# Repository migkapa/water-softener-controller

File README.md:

# Water Softener Controller (rev A)

> [!WARNING]
> **Design only: not built, not tested, not reviewed by an engineer.**
> Low voltage (12 V DC) only. The relay and the field wiring are not isolated or
> rated for mains. If you build it, check everything yourself first; start with
> [Open items](#open-items).

Full film: [`output/product/water_softener_controller.mp4`](output/product/water_softener_controller.mp4)
(21 s, 1280 x 720, no sound).

| Closed | Wiring bay open | See-through | Exploded |
|---|---|---|---|
|  |  |  |  |

Control board for a metered (demand-initiated) water softener valve. An ESP32-C6
drives the valve motor through the regeneration positions, counts treated water
from a turbine flow meter, watches salt level and a leak probe, and keeps time
through power cuts. Supply is 12 V DC.

The project holds the schematic, a first-pass board layout (120 x 80 mm,
4 layers) and a wall-mount enclosure with a wiring bay (127 x 118 x 29 mm). The
layout passes KiCad's design rule check and the enclosure passes a collision
check against the board, but nothing has been reviewed by a layout or mechanical
engineer, built or printed; see "Open items" before ordering anything.

## How this was made

Everything here was produced by Claude Fable 5.2 (Anthropic's model, working in
Claude Code) from a handful of short prompts: the circuit, the board layout and
the router that produced it, the enclosure, the renders and the film. No
engineer has reviewed any of it. Treat it as a demonstration of a hardware
design that rebuilds from scripts, not as a design to build as it stands.

## Files

| Path | What it is |
|---|---|
| `water_softener.kicad_pro`, `water_softener.kicad_sch` | KiCad 10 project and root sheet |
| `power.kicad_sch`, `mcu.kicad_sch`, `drive.kicad_sch`, `sensors.kicad_sch` | The four circuit sheets |
| `water_softener.kicad_sym`, `sym-lib-table` | Project symbol library (DRV8876PWP) |
| `water_softener.kicad_pcb`, `water_softener.kicad_dru` | Board layout and one custom DRC rule |
| `3d/` | Simple 3D bodies for parts KiCad has no model for (module, relay, jack, fuse, RTC, status LED) |
| `enclosure/enclosure.scad` | Enclosure model (OpenSCAD). `board.scad` beside it is written from the board layout |
| `enclosure/stl/` | Parts to print or cut: base, cover, door, button, light pipe, display window |
| `3d/enclosure/` | The same parts, plus stand-ins for display, plugs and screws, as models for the renders |
| `output/water_softener_schematic.pdf` | Schematic, 5 pages |
| `output/sheets/*.png` | One image per schematic sheet |
| `output/water_softener_bom.csv` | BOM: 59 lines, 111 parts |
| `output/water_softener.net`, `output/nets.txt`, `output/erc.json` | Netlist, net summary, ERC report |
| `output/pcb/*.png` | Board renders (top, bottom, angled) and the outer copper layers |
| `output/product/*.png` | The assembled product: front, two angles, rear, wiring bay open, cover off, see-through, exploded |
| `output/product/water_softener_controller.mp4` | 21-second presentation film, 1280 x 720, no sound |
| `output/product/water_softener_controller_x.mp4` | The same film with a different closing card (`scripts/video.py --closing`), as posted on X |
| `output/product/assembly_parts.csv` | Printed parts and bought hardware for one unit |
| `output/product/clearance.txt` | Result of the collision check between enclosure and board |
| `output/water_softener_drc.json` | Board DRC report |
| `docs/preview.gif` | Small animated preview of the film for this page |
| `LICENSE`, `LICENSES/` | Licence summary and the two licence texts |
| `scripts/` | Source of everything above |

Schematic, board and enclosure are written by scripts:

    python3 scripts/build.py              # schematic, ERC, PDF, BOM (a few seconds)
    python3 scripts/build.py --pcb        # the same, then place, route and check the board (about 2 minutes)
    python3 scripts/build.py --product    # the same, then enclosure parts, collision check and renders (about 5 minutes)
    python3 scripts/build.py --video      # the same, then the presentation film (about 30 minutes the first time)

`--product` works on the board file as it is; add `--pcb` to rebuild the board
first. It needs OpenSCAD on the PATH. `--video` needs ffmpeg and the enclosure
models from `--product`; it ray-traces about 500 frames and keeps them in the
system's temporary folder, so a repeat run only renders what changed.

Needs KiCad 10 (tested with 10.0.8), Python 3.9 or later with `pypdf`,
`pdftoppm` (poppler) for the sheet images, OpenSCAD with the Manifold backend
(a 2025 or later build) for the enclosure, and ffmpeg for the film. The
enclosure and film steps run in the Python that has `pcbnew` and also need
numpy and Pillow there; KiCad's macOS bundle includes both.

Tested on macOS only. KiCad is looked up in the usual macOS and Linux places;
set `KICAD_SHARE`, `KICAD_CLI` and `KICAD_PYTHON` if it is somewhere else. The
copper-layer picture needs macOS Quick Look and is skipped elsewhere, and the
film's captions use macOS fonts.

`design.py` holds the circuit, `pcb_layout.py` the board outline, part positions,
net classes and planes, `pcb_route.py` the router and `enclosure/enclosure.scad`
the enclosure. Edit there and rebuild, or edit in KiCad and stop using the
scripts; doing both will overwrite the KiCad edits.

## Blocks

| Block | Main parts | Notes |
|---|---|---|
| 12 V input | J1 barrel jack, J2 terminals, F1 1.5 A PTC, D1 SMAJ16CA, Q1 DMP3099L | Reverse-polarity FET, surge clamp at 26 V |
| Logic supply | D3/D4 SS14, U1 AP63203 (3.3 V, 2 A buck), C3 470 uF | `VSYS` is the diode-OR of +12V and USB VBUS |
| Sensor supply | U2 L78L05 | +5V for field sensors only, about 50 mA continuous |
| MCU | U3 ESP32-C6-MINI-1-N4 | Wi-Fi 6, BLE 5, 802.15.4; all 22 GPIOs used |
| USB-C | J3, U4 USBLC6-2SC6 | Native USB Serial/JTAG for flashing and debug |
| Clock | U5 RV-3028-C7, C15 11 mF backup | Keeps time for days without power |
| User interface | J4 OLED socket, SW2-SW4, D6 RGB LED, LS1 piezo, J5 Qwiic | |
| Valve motor | U6 DRV8876 H-bridge | 1.0 A current limit, analog current feedback |
| Outputs | K1 SPDT relay, Q4 switched 12 V | Alarm / interlock, solenoid or shut-off valve |
| Inputs | Q5-Q8 pass FETs, U7/U8 USBLC6-4SC6 | Valve position x2, flow, salt UART, leak probe |

## Connectors

| Ref | Function | Pins |
|---|---|---|
| J1 | 12 V DC in, 5.5 x 2.1 mm | centre positive |
| J2 | 12 V DC in, terminals | 1 +12 V, 2 GND |
| J3 | USB-C | service port |
| J4 | OLED module socket | 1 GND, 2 3V3, 3 SCL, 4 SDA |
| J5 | Qwiic I2C | 1 GND, 2 3V3, 3 SDA, 4 SCL |
| J6 | Valve motor | 1 OUT1, 2 OUT2 |
| J7 | Relay contacts | 1 NC, 2 NO, 3 COM |
| J8 | Switched 12 V output | 1 +12 V, 2 switched to GND |
| J9 | Valve position | 1 +5 V, 2 HOME, 3 ENC, 4 GND |
| J10 | Flow meter | 1 +5 V, 2 PULSE, 3 GND |
| J11 | Salt level sensor (UART) | 1 +5 V, 2 DATA (sensor TX), 3 AUX, 4 GND |
| J12 | Leak probe | 1 PROBE, 2 GND |

J2 and J6-J12 are Phoenix MC 1,5/x-G-3,5 pluggable headers.

## GPIO map

| GPIO | Net | Use |
|---|---|---|
| 0 | VIN_SENSE | ADC, 0.130 x V(+12V) |
| 1 | MOTOR_ISENSE | ADC, 2.49 V per amp |
| 2 | LEAK_SENSE | ADC, 3.3 V dry, falls when wet |
| 3 | FLOW_PULSE | Flow meter pulses (pulse counter) |
| 4 | BTN_UP | Active low |
| 5 | RELAY_DRV | High = relay on |
| 6 / 7 | I2C_SDA / I2C_SCL | RTC 0x52, OLED, Qwiic |
| 8 | LED_DIN | WS2812B data; strap, pulled high |
| 9 | BTN_SET | Active low; also the BOOT strap |
| 12 / 13 | USB_D_N / USB_D_P | USB Serial/JTAG |
| 14 | BUZZER_DRV | PWM about 4 kHz |
| 15 | AUX_DRV | High = 12 V output on; strap, pulled low |
| 16 | U0TXD | DOWN button through 1 k; ROM boot log on TP7 |
| 17 | SALT_RX | UART RX from the salt sensor |
| 18 / 19 | MOTOR_IN1 / MOTOR_IN2 | 10 forward, 01 reverse, 11 brake, 00 coast |
| 20 | MOTOR_nSLEEP | High = driver enabled (pulled low) |
| 21 | MOTOR_nFAULT | Low = over-current or over-temperature |
| 22 / 23 | POS_HOME / POS_ENC | Active low |

## Design values

- Motor current limit: I = VREF / (R23 x 1000 uA/A) = 2.48 V / 2.49 k = 1.0 A.
  Change R23 to rescale; keep VREF x R23 so that full scale stays under 3.3 V.
- Supply budget at 12 V: motor running 0.2-0.4 A (1.0 A at stall), switched output
  up to 0.5 A, relay 33 mA, logic about 0.1 A. F1 holds 1.5 A, so limit stall time
  in firmware when the switched output is also loaded.
- Hold-up: C3 gives roughly 60 ms at idle after +12V collapses, 20 ms during Wi-Fi
  transmit. Enough to stop the motor and store the cycle step.
- Digital inputs take open-collector, switch or 5 V push-pull sources. Pull-ups are
  2.2 k to 3.3 V (1.5 mA contact current).
- Leak input: 470 k pull-up. A wet probe of 100 k or less reads below 0.6 V.

## What firmware has to do

- Raise `MOTOR_nSLEEP`, wait 1 ms, then drive IN1/IN2. Read `MOTOR_ISENSE` only
  while driving or braking; it reads zero in coast.
- Detect end stops and jams from current (near 2.5 V = at the limit) or from
  missing `POS_ENC` pulses, and stop within a few seconds.
- Below about 9 V on `VIN_SENSE`: stop outputs and save state. Near 0 V with the
  MCU alive means USB-only power; do not run the motor, relay or switched output.
- RV-3028 EEPROM register 37h: enable backup switchover and the trickle charger
  once at first boot. Disable CLKOUT.
- Use the USB Serial/JTAG console. Leave UART0 off so GPIO16 can read the DOWN
  button and GPIO17 can receive the salt sensor at 9600 baud.
- Holding SET while resetting enters the ROM download mode.

## Board

- 120 x 80 mm, 1.6 mm, four M3 holes on a 112 x 72 mm pattern. All parts on the top side.
- Layers: top signals / GND plane / power plane (+12V under the power and motor
  area, +3V3 elsewhere) / bottom signals.
- Field terminals along the bottom edge, 12 V jack on the left, USB-C on the
  right. The module sits at the top edge with its antenna flush to the edge and a
  copper-free strip either side.
- The OLED module plugs into J4 and covers roughly x 26-54, y 4-32 mm of the
  board. Only low parts are placed under it.
- Net classes: signals 0.2 mm, power 0.4 mm, 12 V input and VSYS 0.8 mm, relay
  contacts 1.2 mm with 0.4 mm clearance. Vias 0.6/0.3 mm and 0.8/0.4 mm.
- Routing is automatic (`scripts/pcb_route.py`) except the USB-C escape, which is
  placed by hand: the connector's D+ and D- pads interleave, so the outer pair
  goes round the ESD array U4 and returns on the bottom layer.
- Decoupling and supply pins connect to the planes with a via each; the bulk
  capacitors, buck and switch FETs get two.

## Enclosure

- Outside 126.8 x 117.8 x 28.8 mm; the buttons stand 1 mm proud. Three printed
  shells: base, cover and the door of the wiring bay.
- Front: display window, three buttons (down, up, SET) on the tact switches, a
  light pipe over the status LED, sound holes over the sounder and a pin hole
  over the RESET switch.
- The lower part is the wiring bay. The terminal headers and their plugs sit in
  it behind a door held by two tabs and one screw. A strip above the terminals,
  covered by the door, names each terminal block and pin. Eight cable entries
  in the bottom wall. A partition closes the bay off from the electronics.
- USB-C opening in the right wall (sized for the plug's overmould), 12 V jack in
  the left wall.
- Four M3 screws from the rear clamp base, board and cover together: bosses
  under the board, posts with threaded inserts above it. Three pillars support
  the board under the buttons.
- Wall fixing: a keyhole slot at the top of the rear and two screw holes in the
  floor of the wiring bay.
- The board sits 5 mm above the floor, with 17.8 mm of headroom above it (the
  relay is 15.8 mm tall).

Assembly:

1. Press the five M3 inserts into the four cover posts and the door block.
2. Glue the display window into its recess. With the cover face down, drop the
   light pipe and the three buttons into their sleeves; their flanges keep them
   in once the board is fitted.
3. Plug the OLED module into J4, lay the board onto the cover posts, put the
   base on and fit the four M3 x 12 screws from the rear.
4. Hang the unit on the top wall screw and fix it with two screws through the
   wiring bay.
5. Feed the cables through the bottom entries, wire the plugs, plug them in and
   close the door.

`output/product/assembly_parts.csv` lists the printed parts and the hardware.
Print the base floor down and the cover face down. On the cover, the seat for
the door (label strip, screw block and the pockets for the door tabs) sits
1.8 mm above the bed and needs support. The keyhole pocket in the base is an
11 mm bridge.

## Checked

- KiCad 10.0.8 ERC: 0 errors, 0 warnings on all sheets.
- Every footprint name exists in the stock KiCad libraries.
- Netlist read through net by net against the intended circuit (`output/nets.txt`).
- Against datasheets: DRV8876 PWP pinout, mode pins and 1000 uA/A sense gain;
  AP63203 pinout and component values; ESP32-C6 strapping pins, ADC pins, USB pins
  and reset RC; RV-3028-C7 pin handling.
- Board DRC (KiCad 10.0.8, planes refilled): 0 errors, 0 unconnected items, 0
  differences from the schematic. 20 warnings remain, all for connector
  silkscreen that reaches the board edge.
- Enclosure against board: the build exports the board with its 3D part
  models, samples every surface and tests the points against the enclosure
  solids on a 0.2 mm grid. No part of the board touches the base, cover, door or
  window, and every component keeps at least 0.3 mm from the plastic. The same
  test covers the display module, the wired plugs, buttons and light pipe, and
  the fit of cover, door and window to each other. Result in
  `output/product/clearance.txt`. The check was tried on deliberately wrong
  enclosures: with the ceiling 2.5 mm lower it reports the relay, with 1 mm
  standoffs it reports the through-hole pins, and it reports the sounder's
  leads if they are left untrimmed.
- One DRC rule is relaxed in `water_softener.kicad_dru`: the USB-C receptacle's
  locating pegs sit 0.19 mm from its own ground pads (the manufacturer's land
  pattern), against the board-wide 0.25 mm hole clearance.

## Open items

Parts and circuit:

1. C15 (Seiko CPH3225A) uses the generic 1210 footprint. Confirm against the Seiko
   land pattern.
2. U6 footprint is the HTSSOP-16 PowerPAD variant with a 3 x 3 mm mask opening,
   chosen for TI package PWP0016A (3.3 mm pad). Confirm against the drawing.
3. The 1.0 A motor limit is an assumption. Measure the real valve motor and set R23.
4. D6 must be the WS2812B-2020 V6 revision; earlier ones are not rated at 3.3 V.
5. J4 pin order suits the common GND-VCC-SCL-SDA OLED modules. Some swap GND and VCC.
6. J11 assumes a UART ultrasonic sensor of the A02YYUW type; match the pinout to
   the sensor chosen.
7. L1 is 4.7 uH; the AP63203 datasheet table lists 3.9 uH and allows 2.2-10 uH.
8. Relay contacts and all field wiring are for low voltage only (30 V, 3 A). The
   board has no mains isolation.
9. EMC and safety compliance have not been assessed.

Board, before fabrication:

1. The layout is autorouted and unreviewed. Routes are electrically complete and
   rule-clean, not tidy: expect long diagonals and more vias than a hand layout.
2. Supply copper is minimal. The 12 V path (J1, F1, Q1, C1) and the buck loop
   (U1, C4, L1, C6/C7) would benefit from copper pours and more vias.
3. Some bottom-layer signals cross the split between the +12V and +3V3 planes.
   Harmless at these speeds, worth tidying.
4. No outer-layer ground pours and no stitching vias.
5. Reference designators are on the silkscreen only for ICs, connectors, switches
   and test points; resistors and capacitors need the assembly drawing (F.Fab).
6. Check the mechanical fit of the OLED module, the jack and USB-C overhang, and
   the mounting holes against the enclosure.
7. The 3D bodies in `3d/` are plain boxes for the renders, not accurate models.
8. No Gerber, drill or placement files have been exported yet.

Enclosure, before printing a batch:

1. Nothing has been printed or test-fitted. Mating parts have 0.15-0.2 mm of
   clearance (`fit` in `enclosure.scad`); tune it for the printer and material.
2. OLED modules differ between vendors. The window assumes a 27.3 x 27.8 mm
   module with the middle of the display 10.5 mm below the header row. Measure
   the module in hand and adjust `oled_view`. The module is held only by its
   header; add a foam pad or standoffs under its free end.
3. The relay, jack, module and plugs are box stand-ins sized from their
   datasheets, and the sounder's leads are assumed trimmed to 2.5 mm under the
   board. Check the real parts against the cover before committing.
4. Not sealed. Connector openings and cable entries are open, so this is for a
   dry indoor wall, away from spray and salt. A damp plant room needs gaskets
   and cable glands, or an off-the-shelf IP65 box.
5. No strain relief for the field cables, and unused cable entries stay open.
6. Heat inside the closed box has not been estimated or measured.
7. The legends are engraved 0.3 mm deep; the dark fill in the renders stands
   for paint or a printed label. The window needs black print on its back
   round the display area, as drawn.
8. STL meshes only. OpenSCAD cannot write STEP, so there are no CAD solids of
   the enclosure for further work in a mechanical CAD program.

## Licence

Software under `scripts/` is MIT. The hardware design (the KiCad files,
`enclosure/`, `3d/` and `output/`) is CERN-OHL-P v2. Both are permissive and
come without warranty of any kind. See `LICENSE`.

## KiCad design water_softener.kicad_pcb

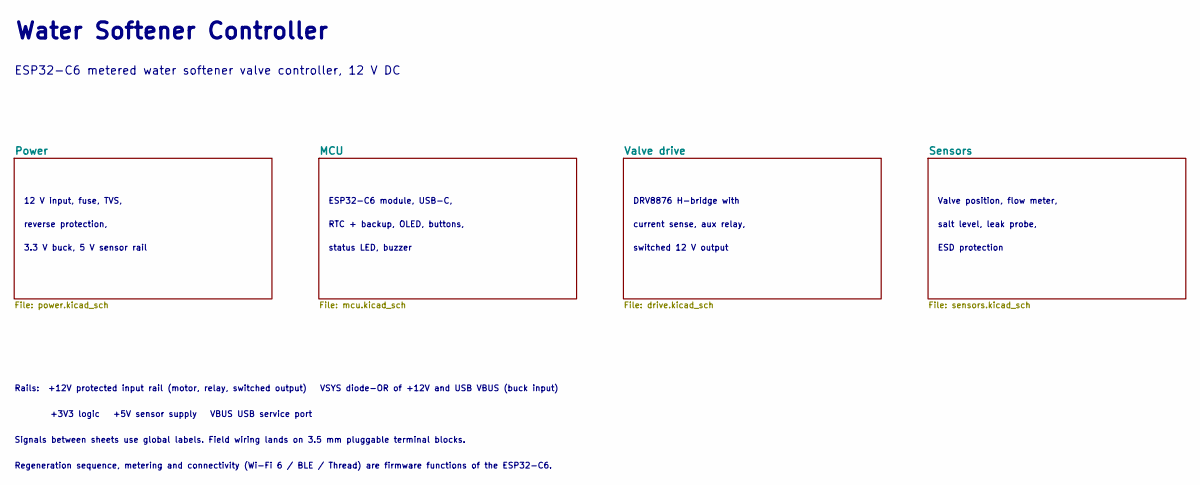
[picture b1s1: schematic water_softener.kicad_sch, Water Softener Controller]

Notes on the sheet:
Rails: +12V protected input rail (motor, relay, switched output) VSYS diode-OR of +12V and USB VBUS (buck input)
Valve position, flow meter,
ESP32-C6 module, USB-C,
+3V3 logic +5V sensor supply VBUS USB service port
3.3 V buck, 5 V sensor rail
Regeneration sequence, metering and connectivity (Wi-Fi 6 / BLE / Thread) are firmware functions of the ESP32-C6.
DRV8876 H-bridge with
ESD protection
salt level, leak probe,
12 V input, fuse, TVS,
Signals between sheets use global labels. Field wiring lands on 3.5 mm pluggable terminal blocks.
ESP32-C6 metered water softener valve controller, 12 V DC
RTC + backup, OLED, buttons,
current sense, aux relay,
status LED, buzzer
Water Softener Controller
reverse protection,
switched 12 V output

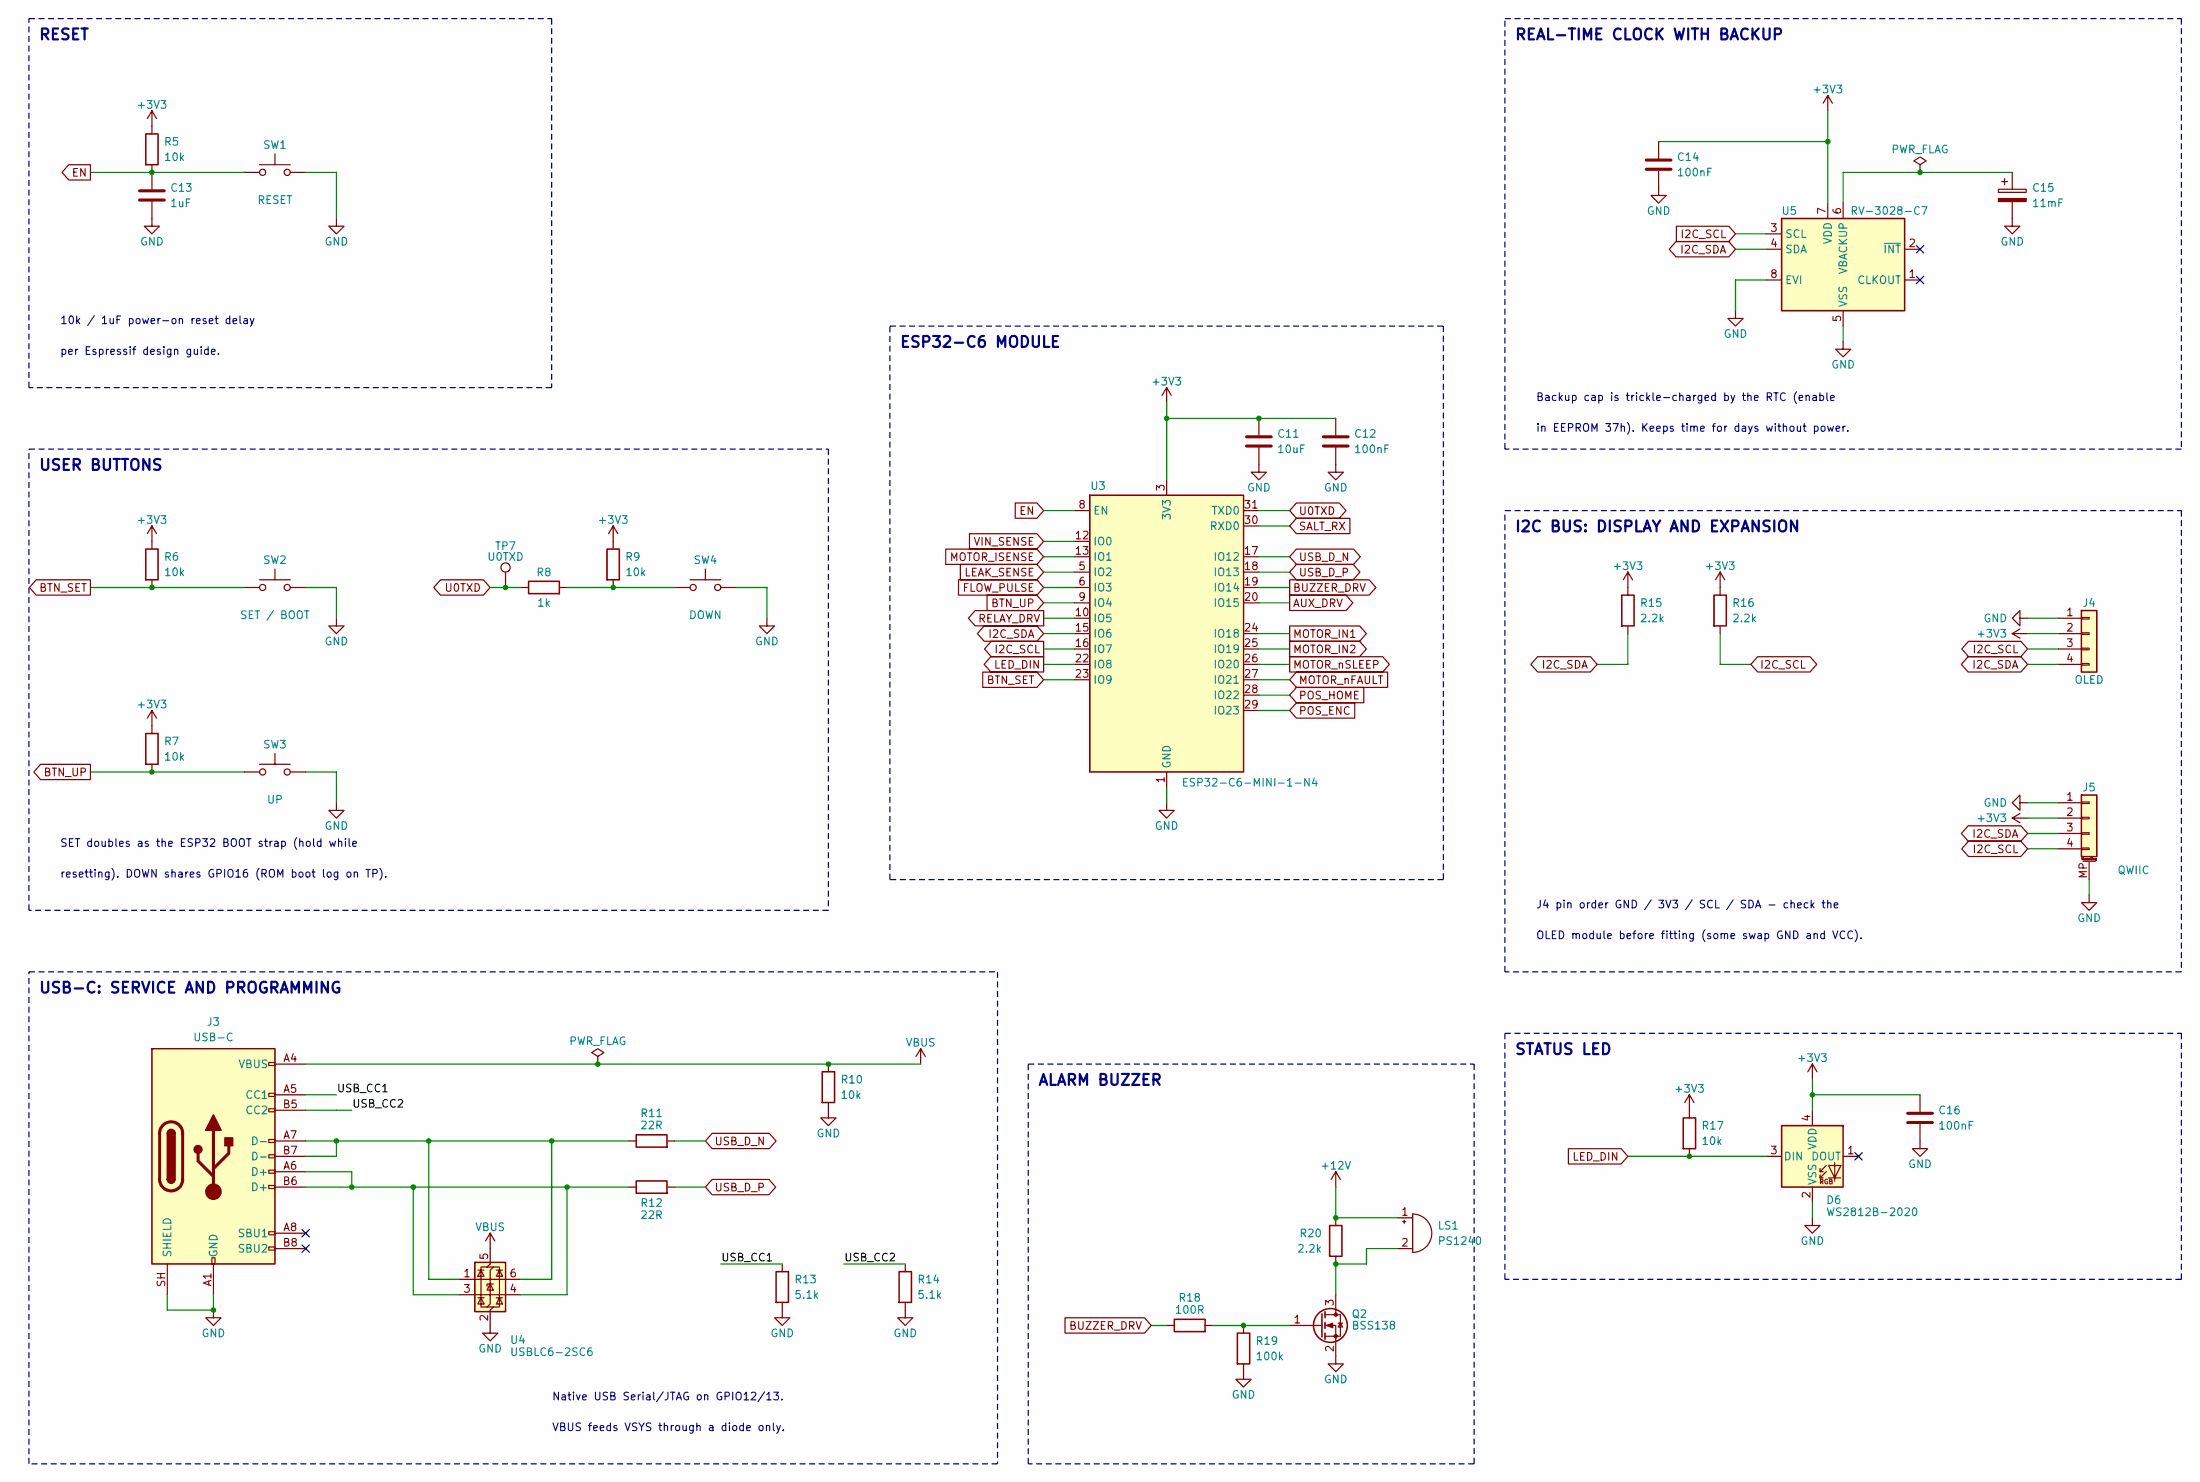
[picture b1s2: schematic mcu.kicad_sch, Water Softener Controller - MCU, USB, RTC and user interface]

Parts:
C11: 10uF; C_0805_2012Metric; Rating 10 V X5R
C12, C14, C16: 100nF; C_0603_1608Metric; Rating 50 V X7R
C13: 1uF; C_0603_1608Metric; Rating 16 V X7R
C15: 11mF; C_1210_3225Metric; Rating 3.3 V EDLC; MPN CPH3225A
D6: WS2812B-2020; LED_WS2812B-2020_PLCC4_2.0x2.0mm; MPN WS2812B-2020 (V6)
J3: USB-C; USB_C_Receptacle_GCT_USB4105-xx-A_16P_TopMnt_Horizontal; MPN USB4105-GF-A
J4: OLED; PinSocket_1x04_P2.54mm_Vertical; MPN 1x04 2.54 mm socket
J5: QWIIC; JST_SH_SM04B-SRSS-TB_1x04-1MP_P1.00mm_Horizontal; MPN SM04B-SRSS-TB
LS1: PS1240; Buzzer_TDK_PS1240P02BT_D12.2mm_H6.5mm; MPN PS1240P02BT
Q2: BSS138; SOT-23; MPN BSS138
R5, R6, R7, R9, R10, R17: 10k; R_0603_1608Metric; Rating 1% 0.1W
R8: 1k; R_0603_1608Metric; Rating 1% 0.1W
R11, R12: 22R; R_0603_1608Metric; Rating 1% 0.1W
R13, R14: 5.1k; R_0603_1608Metric; Rating 1% 0.1W
R15, R16, R20: 2.2k; R_0603_1608Metric; Rating 1% 0.1W
R18: 100R; R_0603_1608Metric; Rating 1% 0.1W
R19: 100k; R_0603_1608Metric; Rating 1% 0.1W
SW1: RESET; SW_SPST_B3U-1000P; MPN B3U-1000P
SW2: SET / BOOT; SW_PUSH_6mm; MPN B3F-1000
SW3: UP; SW_PUSH_6mm; MPN B3F-1000
SW4: DOWN; SW_PUSH_6mm; MPN B3F-1000
TP7: U0TXD; TestPoint_Pad_D1.5mm
U3: ESP32-C6-MINI-1-N4; ESP32-C6-MINI-1; MPN ESP32-C6-MINI-1-N4
U4: USBLC6-2SC6; SOT-23-6; MPN USBLC6-2SC6
U5: RV-3028-C7; MicroCrystal_C7_SON-8_1.5x3.2mm_P0.9mm; MPN RV-3028-C7 32.768kHz 1ppm TA QC

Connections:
+3V3: C11.1, C12.1, C14.1, C16.1, D6.4 (VDD), J4.2, J5.2, R5.1, R6.1, R7.1, R9.1, R15.1, R16.1, R17.1, U3.3 (3V3), U5.7 (VDD); also elsewhere on the board
+12V: LS1.1 (+), R20.1; also elsewhere on the board
/MCU/USB_CC1: J3.A5 (CC1), R13.1
/MCU/USB_CC2: J3.B5 (CC2), R14.1
AUX_DRV: U3.20 (IO15); also elsewhere on the board
BTN_SET: R6.2, SW2.1, U3.23 (IO9)
BTN_UP: R7.2, SW3.1, U3.9 (IO4)
BUZZER_DRV: R18.1, U3.19 (IO14)
EN: C13.1, R5.2, SW1.1, U3.8 (EN)
FLOW_PULSE: U3.6 (IO3); also elsewhere on the board
GND: C11.2, C12.2, C13.2, C14.2, C15.2, C16.2, D6.2 (VSS), J3.A1 (GND), J3.A12 (GND), J3.B1 (GND), J3.B12 (GND), J3.SH (SHIELD), J4.1, J5.1, J5.MP (MountPin), Q2.2 (S), R10.2, R13.2, R14.2, R19.2, SW1.2, SW2.2, SW3.2, SW4.2, U3.1 (GND), U3.2 (GND), U3.11 (GND), U3.14 (GND), U3.36 (GND), U3.37 (GND), U3.38 (GND), U3.39 (GND), U3.40 (GND), U3.41 (GND), U3.42 (GND), U3.43 (GND), U3.44 (GND), U3.45 (GND), U3.46 (GND), U3.47 (GND), U3.48 (GND), U3.49 (GND), U3.50 (GND), U3.51 (GND), U3.52 (GND), U3.53 (GND), U4.2 (GND), U5.5 (VSS), U5.8 (EVI); also elsewhere on the board
I2C_SCL: J4.3, J5.4, R16.2, U3.16 (IO7), U5.3 (SCL)
I2C_SDA: J4.4, J5.3, R15.2, U3.15 (IO6), U5.4 (SDA)
LEAK_SENSE: U3.5 (IO2); also elsewhere on the board
LED_DIN: D6.3 (DIN), R17.2, U3.22 (IO8)
MOTOR_IN1: U3.24 (IO18); also elsewhere on the board
MOTOR_IN2: U3.25 (IO19); also elsewhere on the board
MOTOR_ISENSE: U3.13 (IO1); also elsewhere on the board
MOTOR_nFAULT: U3.27 (IO21); also elsewhere on the board
MOTOR_nSLEEP: U3.26 (IO20); also elsewhere on the board
unnamed: J3.A6 (D+), J3.B6 (D+), R12.1, U4.3 (I/O2), U4.4 (I/O2)
unnamed: J3.A7 (D-), J3.B7 (D-), R11.1, U4.1 (I/O1), U4.6 (I/O1)
unnamed: LS1.2 (-), Q2.3 (D), R20.2
unnamed: Q2.1 (G), R18.2, R19.1
unnamed: R8.2, R9.2, SW4.1
unnamed: C15.1, U5.6 (VBACKUP)
POS_ENC: U3.29 (IO23); also elsewhere on the board
POS_HOME: U3.28 (IO22); also elsewhere on the board
RELAY_DRV: U3.10 (IO5); also elsewhere on the board
SALT_RX: U3.30 (RXD0); also elsewhere on the board
U0TXD: R8.1, TP7.1, U3.31 (TXD0)
USB_D_N: R11.2, U3.17 (IO12)
USB_D_P: R12.2, U3.18 (IO13)
VBUS: J3.A4 (VBUS), J3.A9 (VBUS), J3.B4 (VBUS), J3.B9 (VBUS), R10.1, U4.5 (VBUS); also elsewhere on the board
VIN_SENSE: U3.12 (IO0); also elsewhere on the board

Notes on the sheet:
USB-C: SERVICE AND PROGRAMMING
OLED module before fitting (some swap GND and VCC).
SET doubles as the ESP32 BOOT strap (hold while
STATUS LED
VBUS feeds VSYS through a diode only.
resetting). DOWN shares GPIO16 (ROM boot log on TP).
Backup cap is trickle-charged by the RTC (enable
REAL-TIME CLOCK WITH BACKUP
Native USB Serial/JTAG on GPIO12/13.
in EEPROM 37h). Keeps time for days without power.
10k / 1uF power-on reset delay
RESET
ALARM BUZZER
I2C BUS: DISPLAY AND EXPANSION
J4 pin order GND / 3V3 / SCL / SDA - check the
USER BUTTONS
ESP32-C6 MODULE
per Espressif design guide.

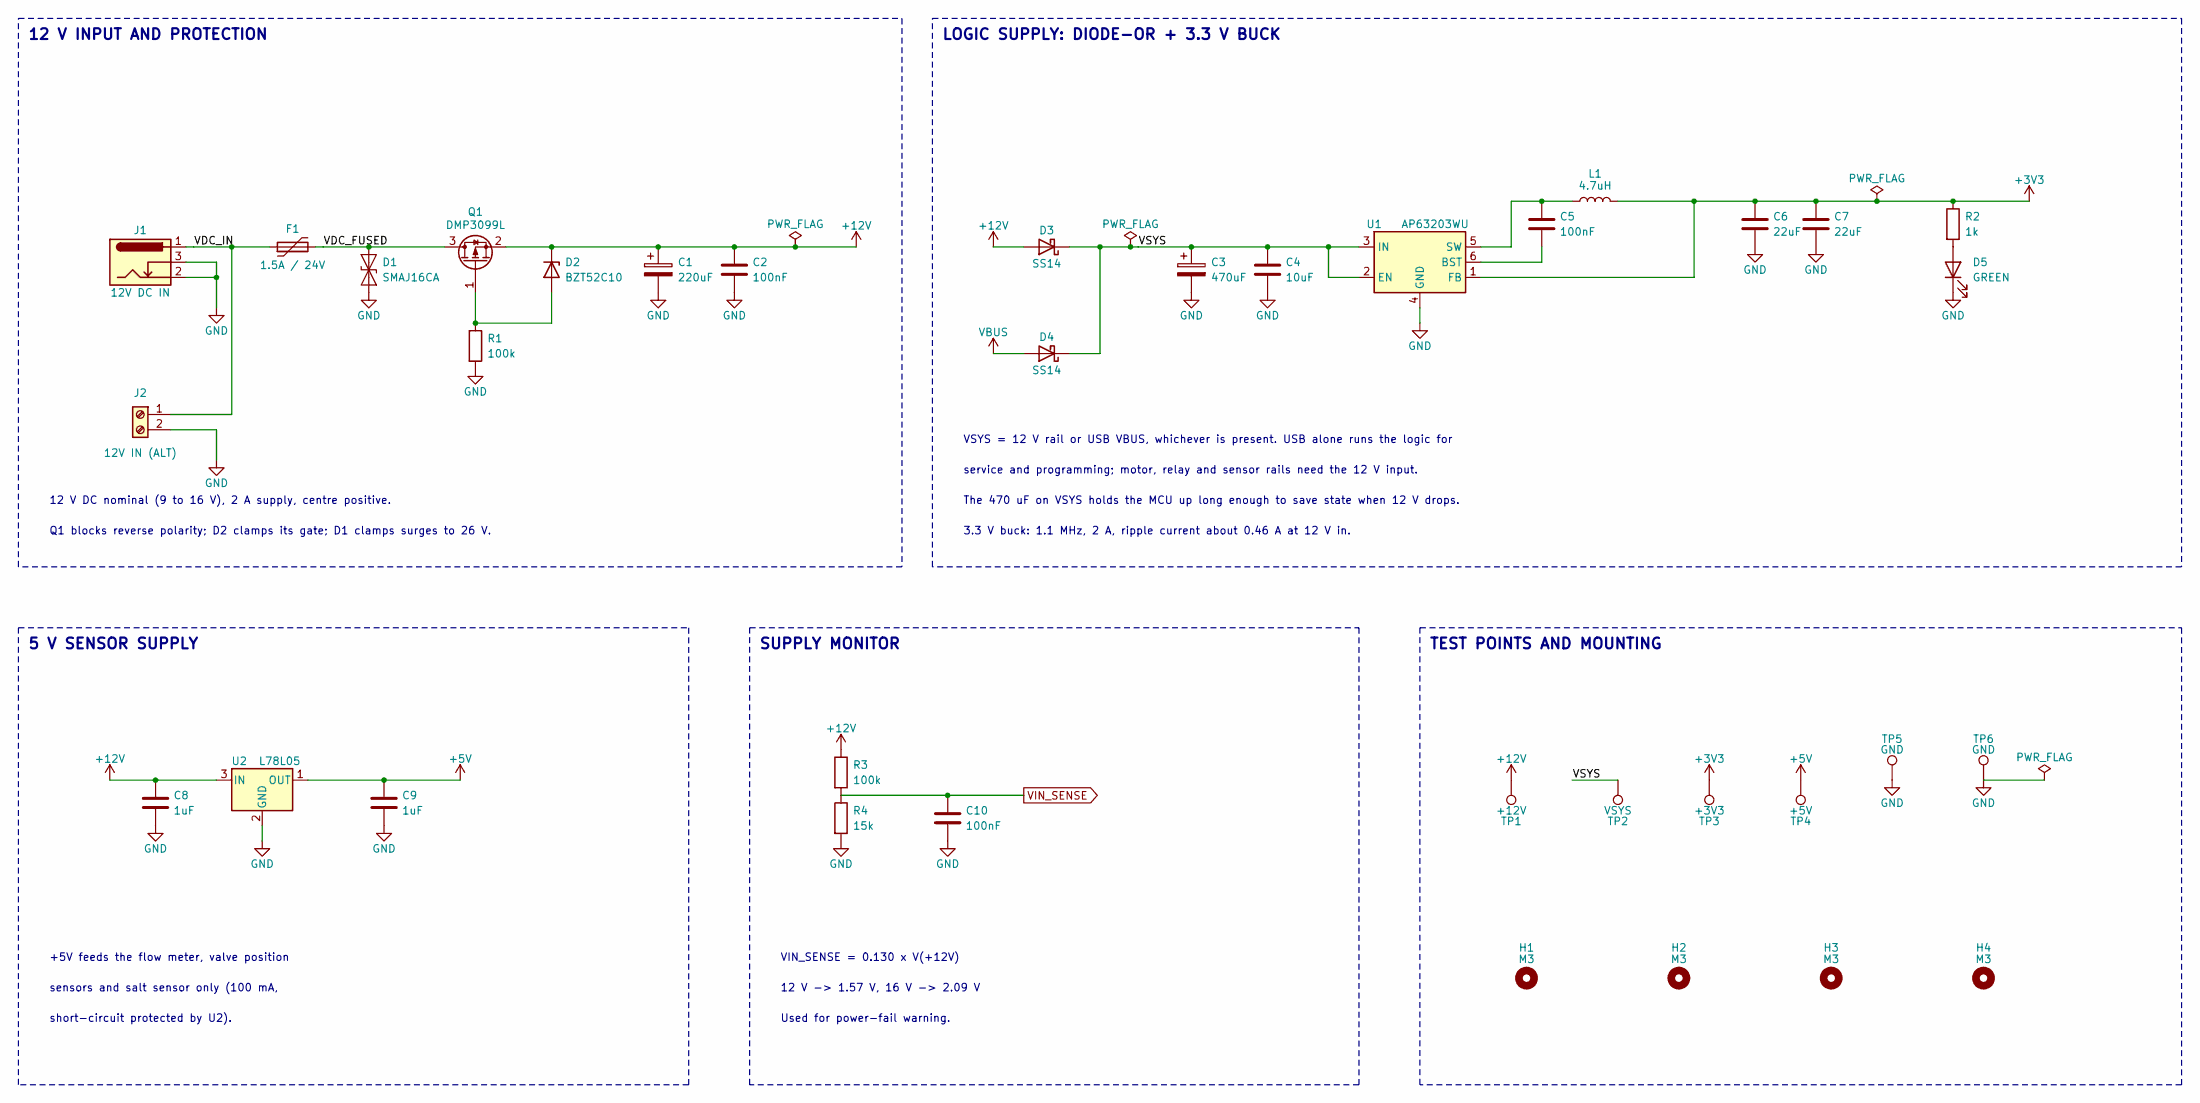
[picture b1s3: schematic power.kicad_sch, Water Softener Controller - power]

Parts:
C1: 220uF; CP_Elec_8x10; Rating 25 V aluminium, 105 C; MPN EEE-FK1E221P
C2, C5, C10: 100nF; C_0603_1608Metric; Rating 50 V X7R
C3: 470uF; CP_Elec_10x10; Rating 25 V aluminium, 105 C; MPN EEE-FK1E471P
C4: 10uF; C_1206_3216Metric; Rating 25 V X7R
C6, C7: 22uF; C_0805_2012Metric; Rating 10 V X5R
C8, C9: 1uF; C_0805_2012Metric; Rating 50 V X7R
D1: SMAJ16CA; D_SMA; Rating 16 V standoff, 400 W, bidirectional; MPN SMAJ16CA
D2: BZT52C10; D_SOD-123; Rating 10 V 5%; MPN BZT52C10-7-F
D3, D4: SS14; D_SMA; Rating 40 V 1 A Schottky; MPN SS14-E3/61T
D5: GREEN; LED_0603_1608Metric; MPN 150060GS75000
F1: 1.5A / 24V; Fuse_1812_4532Metric; Rating 1.5 A hold, 3 A trip, 24 V; MPN MF-MSMF150/24X-2
H1, H2, H3, H4: M3; MountingHole_3.2mm_M3
J1: 12V DC IN; BarrelJack_CUI_PJ-102AH_Horizontal; MPN PJ-102AH
J2: 12V IN (ALT); PhoenixContact_MC_1,5_2-G-3.5_1x02_P3.50mm_Horizontal; MPN 1844210
L1: 4.7uH; L_Coilcraft_XAL4030-XXX; Rating 4.7 uH, Isat 4.5 A, 44 mOhm; MPN XAL4030-472MEC
Q1: DMP3099L; SOT-23; Rating -30 V, 65 mOhm, Vgs +/-20 V; MPN DMP3099L-7
R1, R3: 100k; R_0603_1608Metric; Rating 1% 0.1W
R2: 1k; R_0603_1608Metric; Rating 1% 0.1W
R4: 15k; R_0603_1608Metric; Rating 1% 0.1W
TP1: +12V; TestPoint_Pad_D1.5mm
TP2: VSYS; TestPoint_Pad_D1.5mm
TP3: +3V3; TestPoint_Pad_D1.5mm
TP4: +5V; TestPoint_Pad_D1.5mm
TP5, TP6: GND; TestPoint_Pad_D1.5mm
U1: AP63203WU; TSOT-23-6; MPN AP63203WU-7
U2: L78L05; SOT-89-3; MPN L78L05ABUTR

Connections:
+3V3: C6.1, C7.1, L1.2, R2.1, TP3.1, U1.1 (FB); also elsewhere on the board
+5V: C9.1, TP4.1, U2.1 (OUT); also elsewhere on the board
+12V: C1.1, C2.1, C8.1, D2.1 (K), D3.2 (A), Q1.2 (S), R3.1, TP1.1, U2.3 (IN); also elsewhere on the board
/Power/VDC_FUSED: D1.2 (A2), F1.2, Q1.3 (D)
/Power/VDC_IN: F1.1, J1.1, J2.1
/Power/VSYS: C3.1, C4.1, D3.1 (K), D4.1 (K), TP2.1, U1.2 (EN), U1.3 (IN)
GND: C1.2, C2.2, C3.2, C4.2, C6.2, C7.2, C8.2, C9.2, C10.2, D1.1 (A1), D5.1 (K), J1.2, J1.3, J2.2, R1.2, R4.2, TP5.1, TP6.1, U1.4 (GND), U2.2 (GND); also elsewhere on the board
unnamed: D2.2 (A), Q1.1 (G), R1.1
unnamed: D5.2 (A), R2.2
unnamed: C5.2, U1.6 (BST)
unnamed: C5.1, L1.1, U1.5 (SW)
VBUS: D4.2 (A); also elsewhere on the board
VIN_SENSE: C10.1, R3.2, R4.1; also elsewhere on the board

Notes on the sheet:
5 V SENSOR SUPPLY
12 V -> 1.57 V, 16 V -> 2.09 V
The 470 uF on VSYS holds the MCU up long enough to save state when 12 V drops.
12 V INPUT AND PROTECTION
VSYS = 12 V rail or USB VBUS, whichever is present. USB alone runs the logic for
service and programming; motor, relay and sensor rails need the 12 V input.
sensors and salt sensor only (100 mA,
Q1 blocks reverse polarity; D2 clamps its gate; D1 clamps surges to 26 V.
TEST POINTS AND MOUNTING
SUPPLY MONITOR
3.3 V buck: 1.1 MHz, 2 A, ripple current about 0.46 A at 12 V in.
+5V feeds the flow meter, valve position
LOGIC SUPPLY: DIODE-OR + 3.3 V BUCK
VIN_SENSE = 0.130 x V(+12V)
12 V DC nominal (9 to 16 V), 2 A supply, centre positive.
Used for power-fail warning.
short-circuit protected by U2).

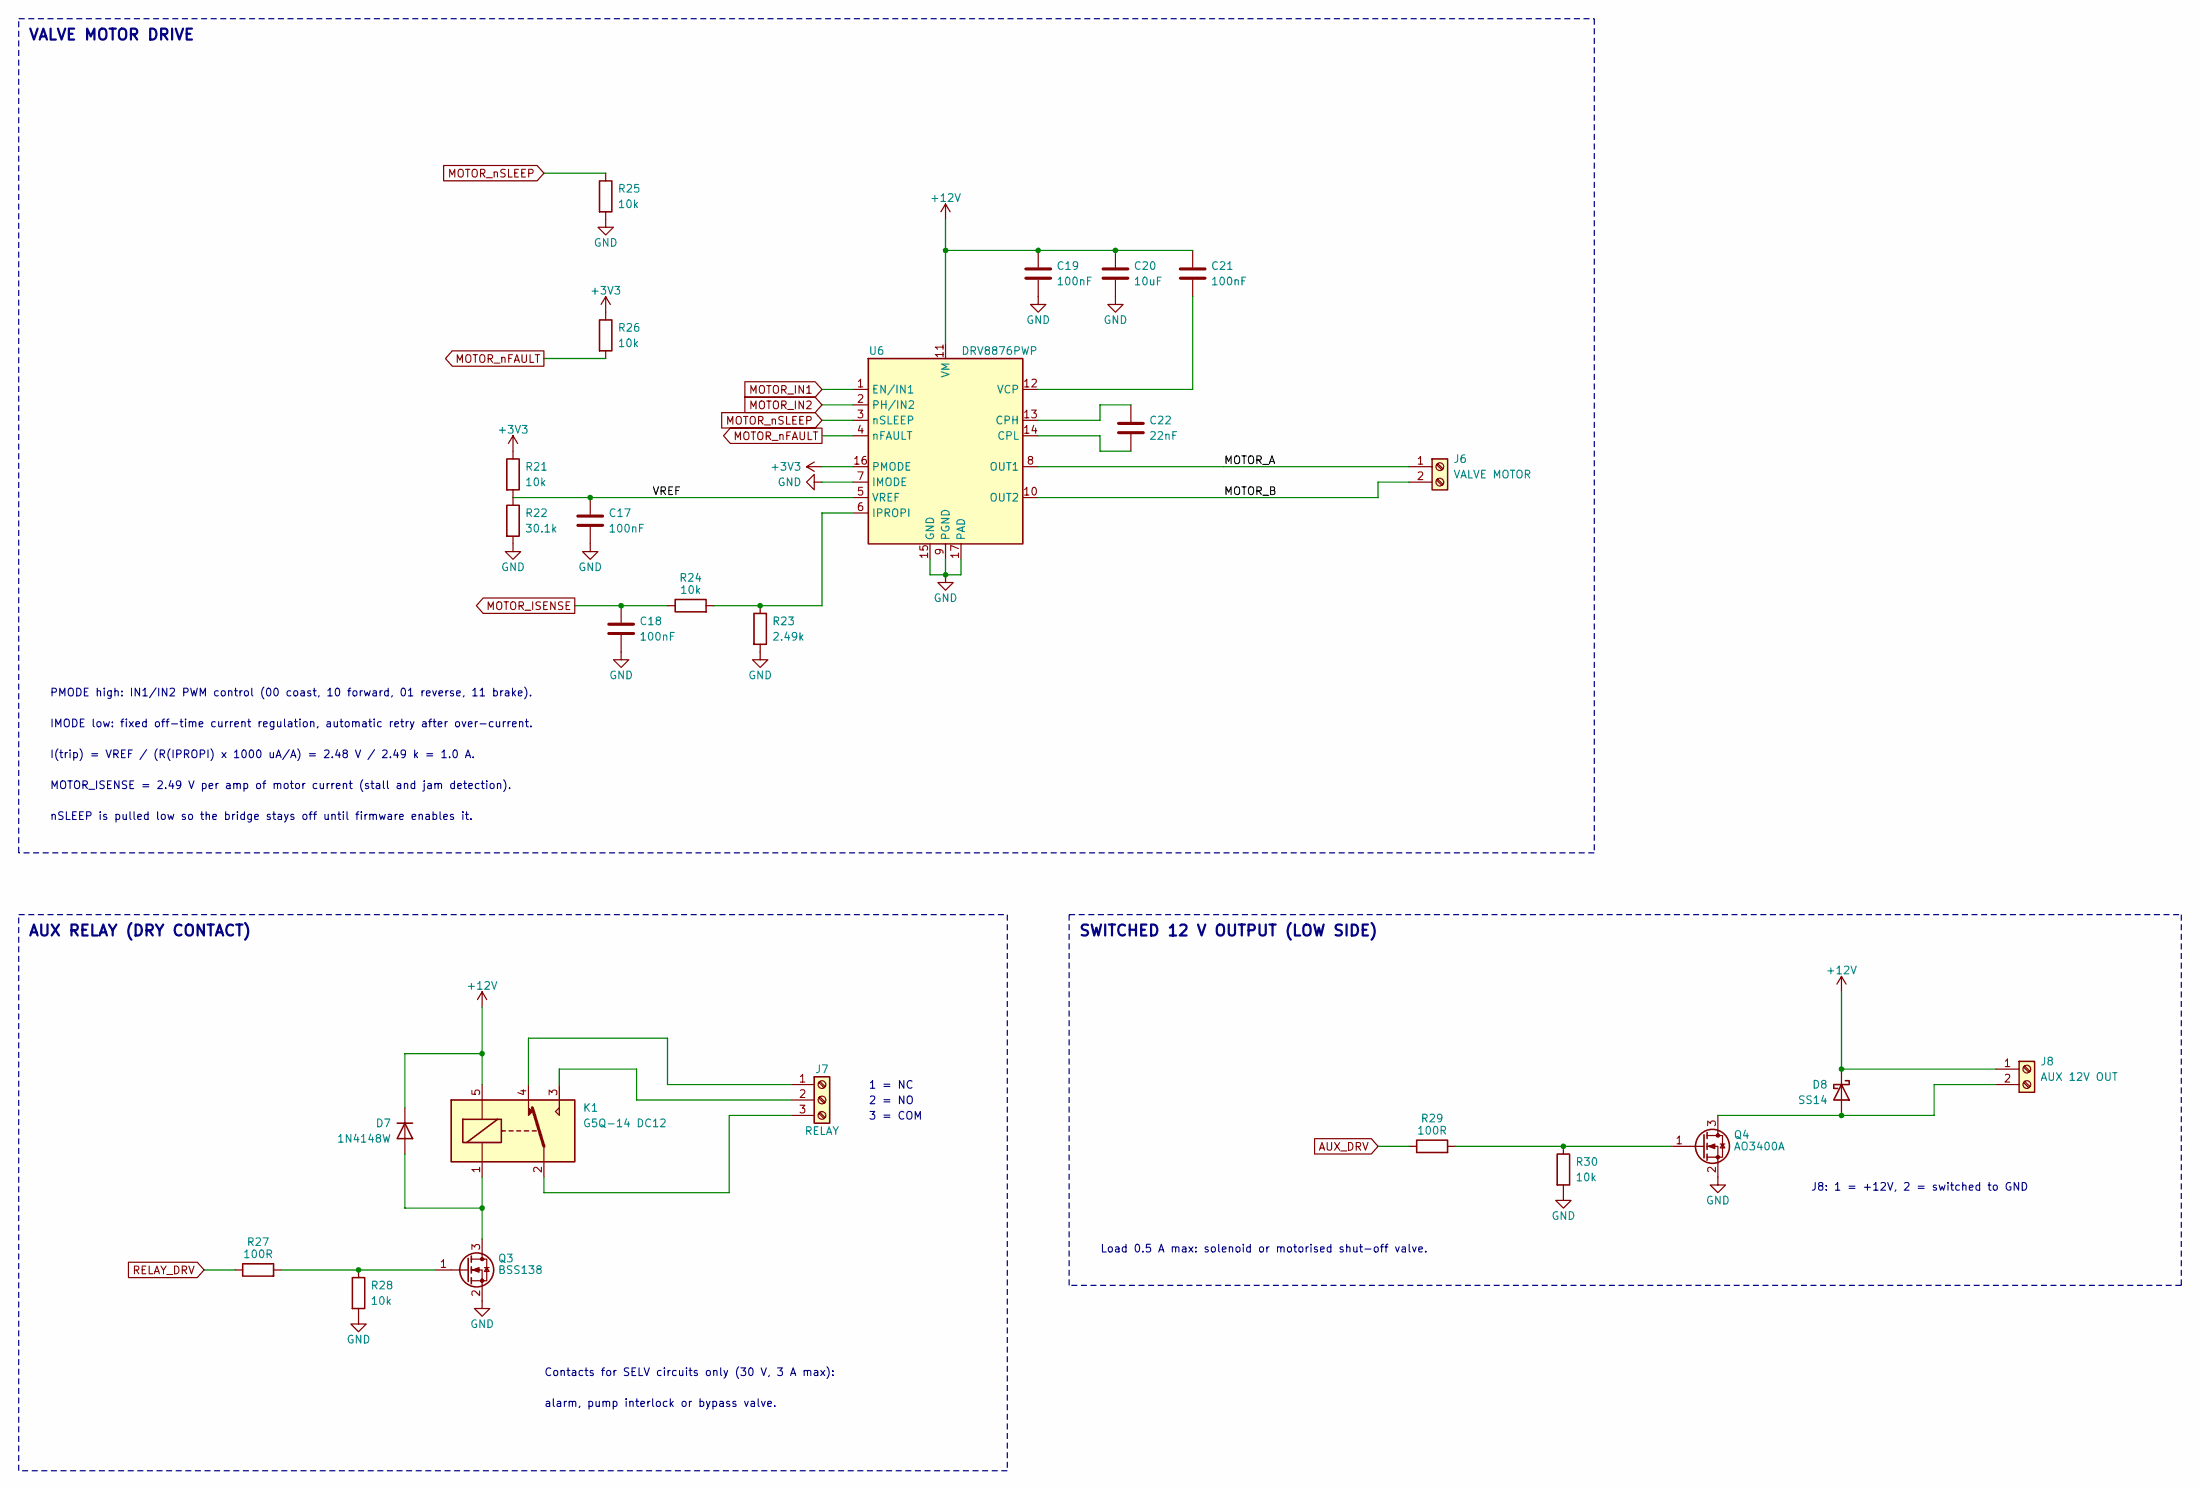
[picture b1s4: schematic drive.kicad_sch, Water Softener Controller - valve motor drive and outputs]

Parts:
C17, C18, C19, C21: 100nF; C_0603_1608Metric; Rating 50 V X7R
C20: 10uF; C_1206_3216Metric; Rating 25 V X7R
C22: 22nF; C_0603_1608Metric; Rating 50 V X7R
D7: 1N4148W; D_SOD-123; MPN 1N4148W-7-F
D8: SS14; D_SMA; Rating 40 V 1 A Schottky; MPN SS14-E3/61T
J6: VALVE MOTOR; PhoenixContact_MC_1,5_2-G-3.5_1x02_P3.50mm_Horizontal; MPN 1844210
J7: RELAY; PhoenixContact_MC_1,5_3-G-3.5_1x03_P3.50mm_Horizontal; MPN 1844223
J8: AUX 12V OUT; PhoenixContact_MC_1,5_2-G-3.5_1x02_P3.50mm_Horizontal; MPN 1844210
K1: G5Q-14 DC12; Relay_SPDT_Omron-G5Q-1; Rating 12 V coil 33 mA, SPDT; MPN G5Q-14 DC12
Q3: BSS138; SOT-23; MPN BSS138
Q4: AO3400A; SOT-23; MPN AO3400A
R21, R24, R25, R26, R28, R30: 10k; R_0603_1608Metric; Rating 1% 0.1W
R22: 30.1k; R_0603_1608Metric; Rating 1% 0.1W
R23: 2.49k; R_0603_1608Metric; Rating 1% 0.1W
R27, R29: 100R; R_0603_1608Metric; Rating 1% 0.1W
U6: DRV8876PWP; HTSSOP-16-1EP_4.4x5mm_P0.65mm_EP3.4x5mm_Mask3x3mm_ThermalVi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; MPN DRV8876PWPR

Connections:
+3V3: R21.1, R26.1, U6.16 (PMODE); also elsewhere on the board
+12V: C19.1, C20.1, C21.1, D7.1 (K), D8.1 (K), J8.1, K1.5, U6.11 (VM); also elsewhere on the board
/Valve drive/MOTOR_A: J6.1, U6.8 (OUT1)
/Valve drive/MOTOR_B: J6.2, U6.10 (OUT2)
/Valve drive/VREF: C17.1, R21.2, R22.1, U6.5 (VREF)
AUX_DRV: R29.1; also elsewhere on the board
GND: C17.2, C18.2, C19.2, C20.2, Q3.2 (S), Q4.2 (S), R22.2, R23.2, R25.2, R28.2, R30.2, U6.7 (IMODE), U6.9 (PGND), U6.15 (GND), U6.17 (PAD); also elsewhere on the board
MOTOR_IN1: U6.1 (EN/IN1); also elsewhere on the board
MOTOR_IN2: U6.2 (PH/IN2); also elsewhere on the board
MOTOR_ISENSE: C18.1, R24.1; also elsewhere on the board
MOTOR_nFAULT: R26.2, U6.4 (nFAULT); also elsewhere on the board
MOTOR_nSLEEP: R25.1, U6.3 (nSLEEP); also elsewhere on the board
unnamed: D7.2 (A), K1.1, Q3.3 (D)
unnamed: D8.2 (A), J8.2, Q4.3 (D)
unnamed: J7.1, K1.4
unnamed: J7.2, K1.3
unnamed: J7.3, K1.2
unnamed: Q3.1 (G), R27.2, R28.1
unnamed: Q4.1 (G), R29.2, R30.1
unnamed: C22.1, U6.13 (CPH)
unnamed: C22.2, U6.14 (CPL)
unnamed: R23.1, R24.2, U6.6 (IPROPI)
unnamed: C21.2, U6.12 (VCP)
RELAY_DRV: R27.1; also elsewhere on the board

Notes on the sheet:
3 = COM
AUX RELAY (DRY CONTACT)
MOTOR_ISENSE = 2.49 V per amp of motor current (stall and jam detection).
SWITCHED 12 V OUTPUT (LOW SIDE)
IMODE low: fixed off-time current regulation, automatic retry after over-current.
2 = NO
alarm, pump interlock or bypass valve.
nSLEEP is pulled low so the bridge stays off until firmware enables it.
1 = NC
VALVE MOTOR DRIVE
PMODE high: IN1/IN2 PWM control (00 coast, 10 forward, 01 reverse, 11 brake).
J8: 1 = +12V, 2 = switched to GND
Load 0.5 A max: solenoid or motorised shut-off valve.
Contacts for SELV circuits only (30 V, 3 A max):
I(trip) = VREF / (R(IPROPI) x 1000 uA/A) = 2.48 V / 2.49 k = 1.0 A.
